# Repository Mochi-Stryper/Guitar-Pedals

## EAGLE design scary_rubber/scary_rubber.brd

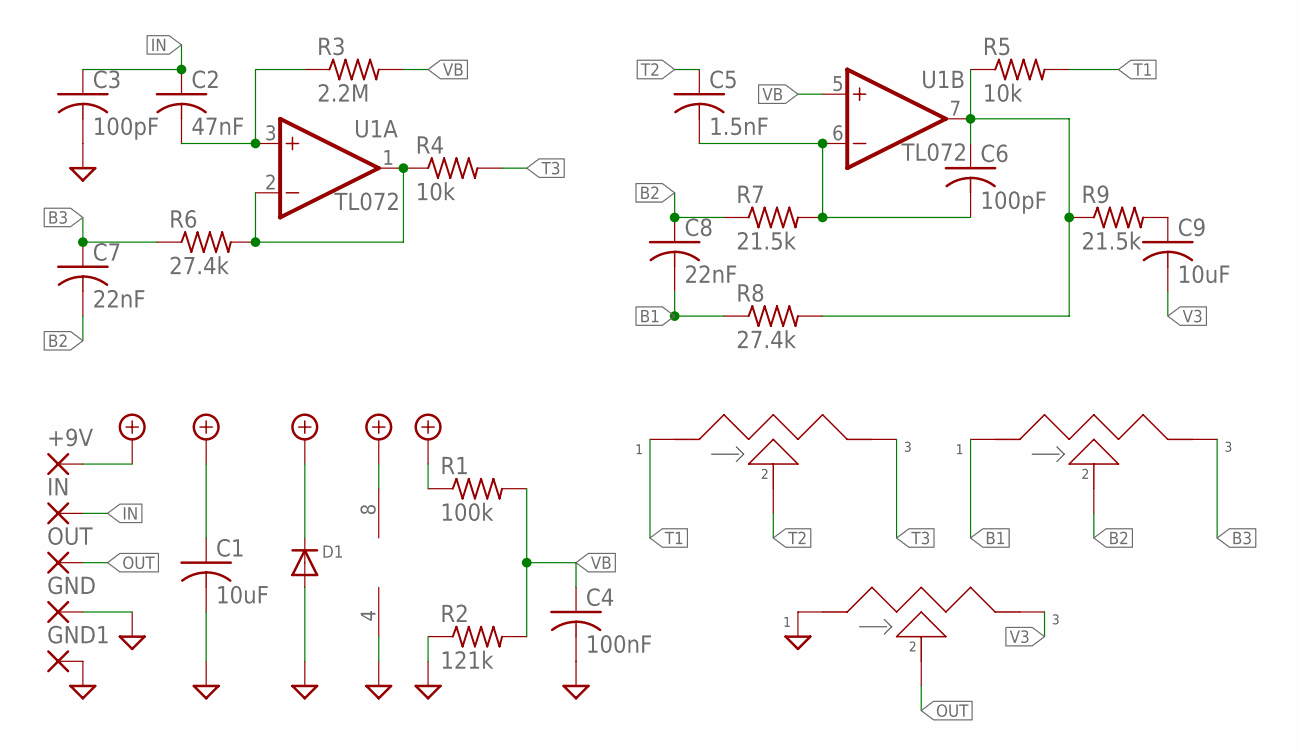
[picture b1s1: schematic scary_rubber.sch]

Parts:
+9V: SMD2; SMD1,27-2,54
BASS: B100k; POT_9MM_SMD
C1, C9: 10uF; C1206
C2: 47nF; C0603
C3, C6: 100pF; C0603
C4: 100nF; C0603
C5: 1.5nF; C0603
C7, C8: 22nF; C0603
D1: DIODESOD-123; SOD-123
GND, GND1: SMD2; SMD1,27-2,54
IN: SMD2; SMD1,27-2,54
OUT: SMD2; SMD1,27-2,54
R1: 100k; R0603
R2: 121k; R0603
R3: 2.2M; R0603
R4, R5: 10k; R0603
R6, R8: 27.4k; R0603
R7, R9: 21.5k; R0603
TREB: B100k; POT_9MM_SMD
U1: TL072; TSSOP-8
VOLU: B100k; POT_9MM_SMD

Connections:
+9V: +9V.1, C1.1, D1.C, R1.1, U1.8 (V+)
B1: BASS.1, C8.2, R8.1
B2: BASS.2, C7.2, C8.1, R7.1
B3: BASS.3, C7.1, R6.1
GND: C1.2, C3.2, C4.2, D1.A, GND.1, GND1.1, R2.1, U1.4 (V-), VOLU.1
IN: C2.1, C3.1, IN.1
unnamed: C2.2, R3.1, U1.3 (+IN)
unnamed: R4.1, R6.2, U1.1 (OUT), U1.2 (-IN)
unnamed: C5.2, C6.2, R7.2, U1.6 (-IN)
unnamed: C6.1, R5.1, R8.2, R9.1, U1.7 (OUT)
unnamed: C9.1, R9.2
OUT: OUT.1, VOLU.2
T1: R5.2, TREB.1
T2: C5.1, TREB.2
T3: R4.2, TREB.3
V3: C9.2, VOLU.3
VB: C4.1, R1.2, R2.2, R3.2, U1.5 (+IN)

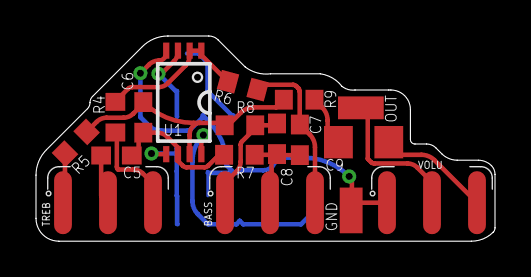
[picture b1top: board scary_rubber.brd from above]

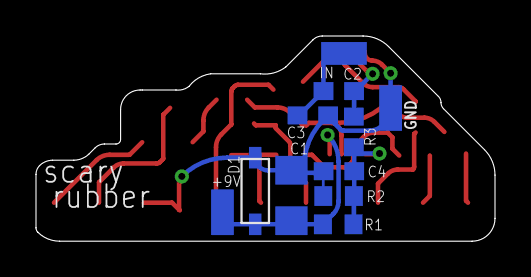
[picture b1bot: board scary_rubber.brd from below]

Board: 2 copper layers, 25.5 x 11.4 mm, 28 parts (11 on the bottom side), 17 nets.

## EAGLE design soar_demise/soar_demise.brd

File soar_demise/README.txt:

Devi Ever
Soda Meiser
Vintage Fuzz Master
The polarity of the 2907 transistor determines the sonic characteristics of the resultant fuzz. Never bent the leads on SOT23? Me neither, but give it a shot and tell me if it's worth it.
Bare bones. No tone control. No polarity protection.

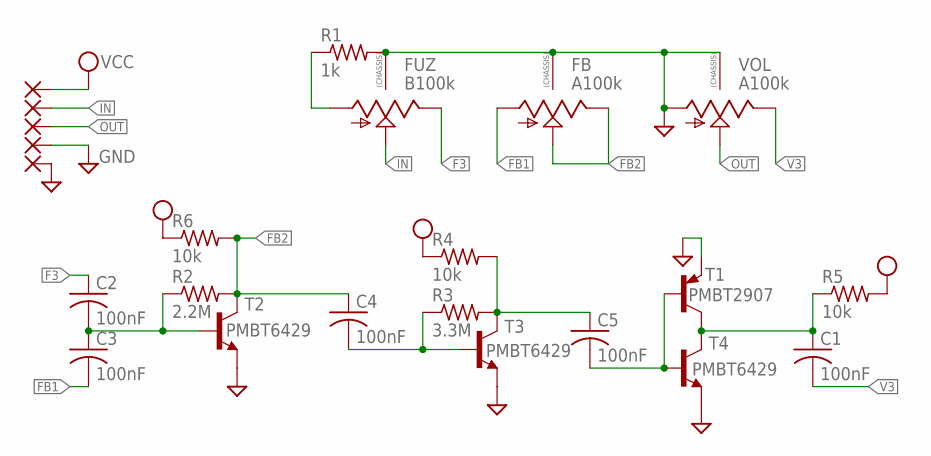
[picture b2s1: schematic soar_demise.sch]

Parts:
C1, C2, C3, C4, C5: 100nF; C0805
FB: A100k; 9MM_SNAP-IN_POT
FUZ: B100k; 9MM_SNAP-IN_POT
PAD1, PAD2, PAD3, PAD4, PAD5: 1,6/0,8
R1: 1k; R0805
R2: 2.2M; R0805
R3: 3.3M; R0805
R4, R5, R6: 10k; R0805
T1: PMBT2907; SOT23-BEC
T2, T3, T4: PMBT6429; SOT23-BEC
VOL: A100k; 9MM_SNAP-IN_POT

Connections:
F3: C2.1, FUZ.3 (E)
FB1: C3.2, FB.1 (A)
FB2: C4.1, FB.2 (S), FB.3 (E), R2.2, R6.2, T2.C
GND: FB.CHASSIS1, FB.CHASSIS2, FUZ.CHASSIS1, FUZ.CHASSIS2, PAD4.1, PAD5.1, R1.2, T1.E, T2.E, T3.E, T4.E, VOL.1 (A), VOL.CHASSIS1, VOL.CHASSIS2
IN: FUZ.2 (S), PAD2.1
unnamed: C1.1, R5.1, T1.C, T4.C
unnamed: C2.2, C3.1, R2.1, T2.B
unnamed: C5.1, R3.2, R4.2, T3.C
unnamed: FUZ.1 (A), R1.1
unnamed: C4.2, R3.1, T3.B
unnamed: C5.2, T1.B, T4.B
OUT: PAD3.1, VOL.2 (S)
V3: C1.2, VOL.3 (E)
VCC: PAD1.1, R4.1, R5.2, R6.1

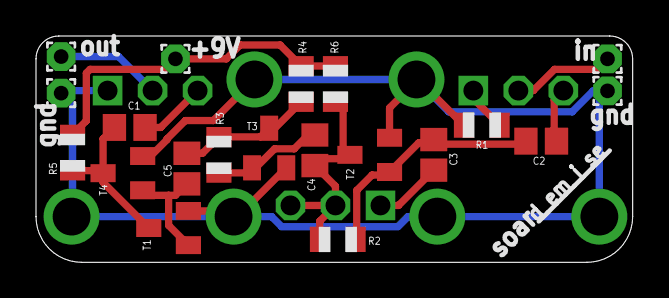
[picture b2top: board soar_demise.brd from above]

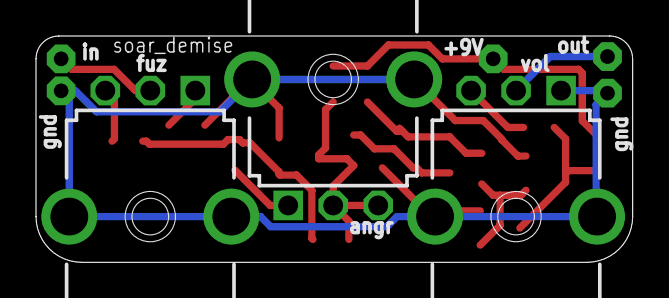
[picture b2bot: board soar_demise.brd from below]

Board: 2 copper layers, 33.1 x 12.6 mm, 23 parts (3 on the bottom side), 14 nets.

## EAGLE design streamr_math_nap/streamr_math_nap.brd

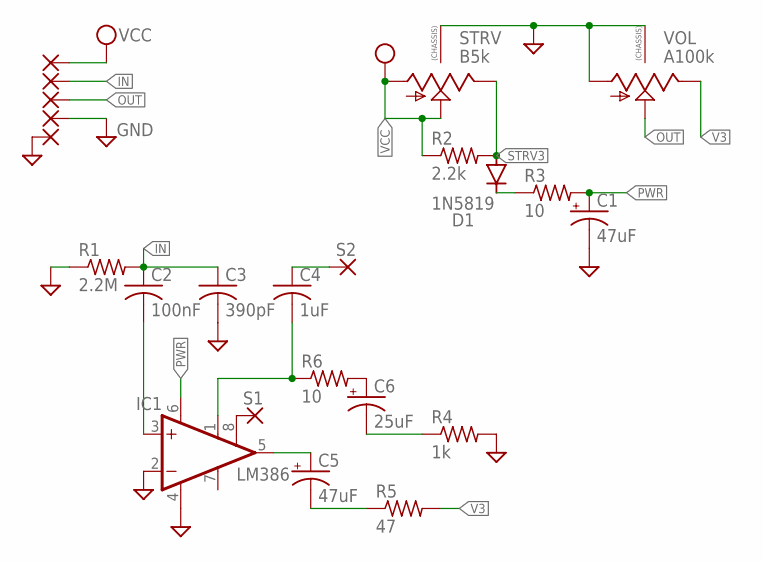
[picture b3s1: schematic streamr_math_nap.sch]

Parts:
C1, C5: 47uF; PAN_C_SMD+THRU
C2: 100nF; C0805
C3: 390pF; C0805
C4: 1uF; C0805
C6: 25uF; PAN_C_SMD+THRU
D1: 1N5819; SOD123
IC1: LM386; SO08
PAD1, PAD2, PAD3, PAD4, PAD5: 1,6/0,8
R1: 2.2M; R0805
R2: 2.2k; R1206
R3, R6: 10; R1206
R4: 1k; R1206
R5: 47; R1206
S1: S1; 1,6/0,8
S2: S2; 1,6/0,8
STRV: B5k; 9MM_SNAP-IN_POT
VOL: A100k; 9MM_SNAP-IN_POT

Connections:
GND: C1.-, C1.-- (-), C3.2, IC1.2 (-IN), IC1.4 (GND), PAD4.1, PAD5.1, R1.1, R4.2, STRV.CHASSIS1, STRV.CHASSIS2, VOL.1 (A), VOL.CHASSIS1, VOL.CHASSIS2
IN: C2.1, C3.1, PAD2.1, R1.2
unnamed: IC1.8 (GAIN), S1.1
unnamed: C2.2, IC1.3 (+IN)
unnamed: D1.C, R3.1
unnamed: C4.2, IC1.1 (GAIN), R6.1
unnamed: C5.+, C5.++ (+), IC1.5 (OUT)
unnamed: C5.-, C5.-- (-), R5.1
unnamed: C6.+, C6.++ (+), R6.2
unnamed: C6.-, C6.-- (-), R4.1
unnamed: C4.1, S2.1
OUT: PAD3.1, VOL.2 (S)
PWR: C1.+, C1.++ (+), IC1.6 (VS), R3.2
STRV3: D1.A, R2.2, STRV.3 (E)
V3: R5.2, VOL.3 (E)
VCC: PAD1.1, R2.1, STRV.1 (A), STRV.2 (S)

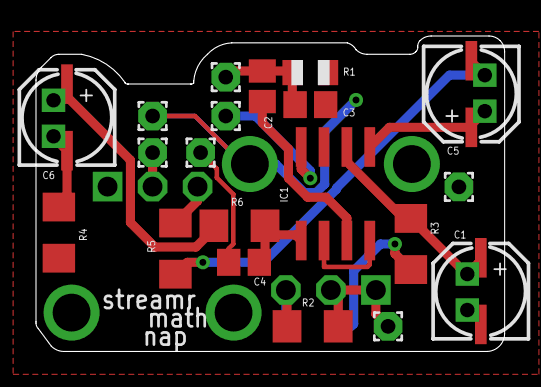
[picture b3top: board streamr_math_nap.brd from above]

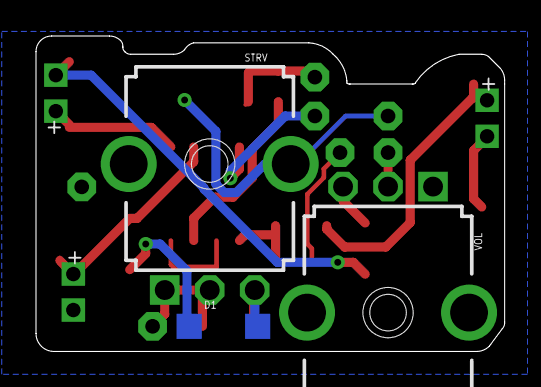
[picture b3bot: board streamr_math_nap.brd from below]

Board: 2 copper layers, 26.0 x 17.5 mm, 23 parts (3 on the bottom side), 16 nets.

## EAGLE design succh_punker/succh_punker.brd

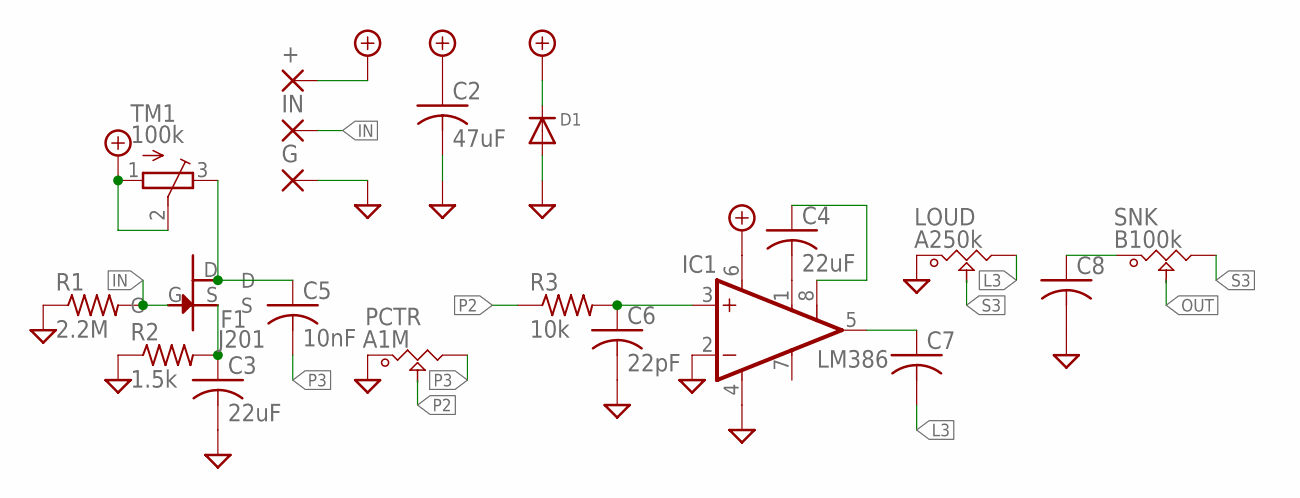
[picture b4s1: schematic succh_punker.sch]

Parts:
+: SMD2; SMD1,27-2,54
C2: 47uF; C1210
C3, C4: 22uF; C1210
C5: 10nF; C0603
C6: 22pF; C0603
C7, C8: C-USC0603; C0603
D1: DIODESOD-123; SOD-123
F1: J201; MMBFJ201
G: SMD2; SMD1,27-2,54
IC1: LM386; SO08
IN: SMD2; SMD1,27-2,54
LOUD: A250k; POT_9MM_SMD
PCTR: A1M; POT_9MM_SMD
R1: 2.2M; R0603
R2: 1.5k; R0603
R3: 10k; R0603
SNK: B100k; POT_9MM_SMD
TM1: 100k; TC33X

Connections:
+9V: +.1, C2.1, D1.C, IC1.6 (VS), TM1.1 (A), TM1.2 (S)
F1_D: C5.1, F1.D, TM1.3 (E)
F1_S: C3.1, F1.S, R2.2
GND: C2.2, C3.2, C6.2, C8.2, D1.A, G.1, IC1.2 (-IN), IC1.4 (GND), LOUD.1, PCTR.1, R1.1, R2.1
IN: F1.G, IN.1, R1.2
L3: C7.2, LOUD.3
unnamed: C4.2, IC1.1 (GAIN)
unnamed: C8.1, SNK.1
unnamed: C4.1, IC1.8 (GAIN)
OA_+: C6.1, IC1.3 (+IN), R3.2
OA_O: C7.1, IC1.5 (OUT)
OUT: SNK.2
P2: PCTR.2, R3.1
P3: C5.2, PCTR.3
S3: LOUD.2, SNK.3

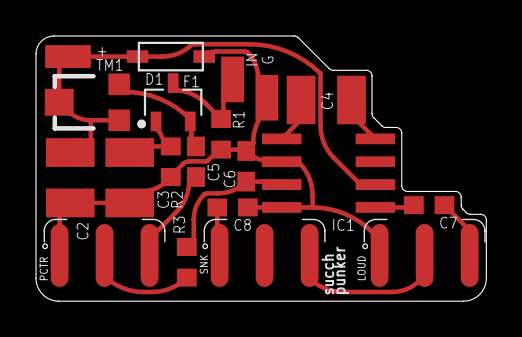
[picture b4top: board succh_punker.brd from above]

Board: 2 copper layers, 25.0 x 14.7 mm, 20 parts (0 on the bottom side), 14 nets.

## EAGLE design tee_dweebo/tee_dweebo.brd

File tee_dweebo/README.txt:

Boss
BD-2 Blues Driver
Notes:
Registered an airwire across the lugs of the DRV pot. This should be resolved via the pot's chassis ground. However, if an external potentiometer is used, then it's advisable to run a ground airwire to the chassis lugs. Best of luck.

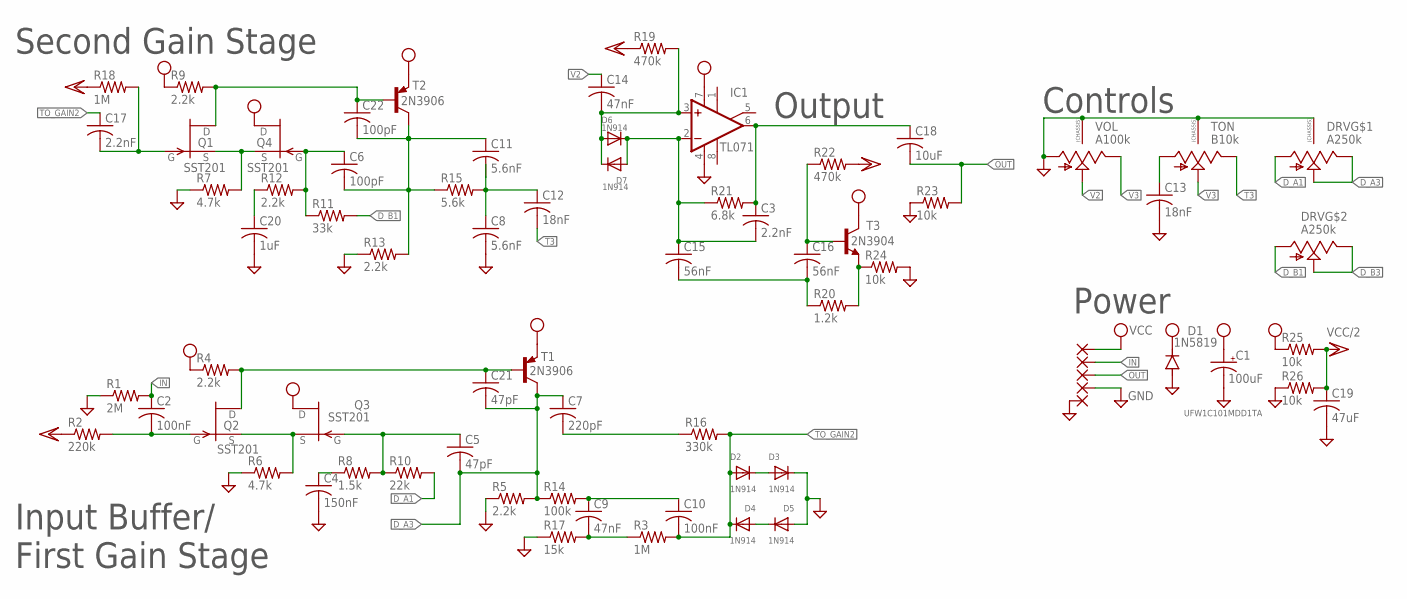
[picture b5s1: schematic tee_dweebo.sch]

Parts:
C1: 100uF; ELEC10UF_SM
C2, C10: 100nF; C0402
C3, C17: 2.2nF; C0402
C4: 150nF; C0402
C5, C21: 47pF; C0402
C6, C22: 100pF; C0402
C7: 220pF; C0402
C8, C11: 5.6nF; C0402
C9, C14: 47nF; C0402
C12, C13: 18nF; C0402
C15, C16: 56nF; C0402
C18: 10uF; C0805
C19: 47uF; C1206
C20: 1uF; C0603
D1: 1N5819; SOD123
D2, D3, D4, D5, D6, D7: 1N914; SOD-323F
DRV: A250k; DUAL_9MM_SNAP-IN_POT
IC1: TL071; SO08
PAD1, PAD2, PAD3, PAD4, PAD5: 1,6/0,8
Q1, Q2, Q3, Q4: SST201; SOT23
R1: 2M; R0402
R2: 220k; R0402
R3, R18: 1M; R0402
R4, R5, R9, R12, R13: 2.2k; R0402
R6, R7: 4.7k; R0402
R8: 1.5k; R0402
R10: 22k; R0402
R11: 33k; R0402
R14: 100k; R0402
R15: 5.6k; R0402
R16: 330k; R0402
R17: 15k; R0402
R19, R22: 470k; R0402
R20: 1.2k; R0402
R21: 6.8k; R0402
R23, R24, R25, R26: 10k; R0402
T1, T2: 2N3906; SOT23-BEC
T3: 2N3904; SOT23-BEC
TON: B10k; 9MM_SNAP-IN_POT
VOL: A100k; 9MM_SNAP-IN_POT

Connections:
D_A1: DRV.1 (A), R10.2
D_A3: C5.2, C7.1, C21.2, DRV.2 (S), DRV.3 (E), R5.2, R14.1, T1.C
D_B1: DRV.1B (A), R11.2
D_B3: DRV.2B (S), DRV.3B (E)
GND: C1.-, C4.2, C8.2, C13.2, C19.2, C20.2, D1.A, D3.C, D5.A, DRV.CHASSIS1, DRV.CHASSIS2, IC1.4 (V-), PAD4.1, PAD5.1, R1.1, R5.1, R6.1, R7.1, R13.1, R17.1, R23.1, R24.2, R26.1, TON.CHASSIS1, TON.CHASSIS2, VOL.1 (A), VOL.CHASSIS1, VOL.CHASSIS2
IN: C2.1, PAD2.1, R1.2
unnamed: Q2.2 (S), Q3.2 (S), R6.2
unnamed: C2.2, Q2.3 (G), R2.2
unnamed: C21.1, Q2.1 (D), R4.2, T1.B
unnamed: C4.1, R8.1
unnamed: C5.1, Q3.3 (G), R8.2, R10.1
unnamed: C9.1, C10.1, R14.2
unnamed: C9.2, R3.1, R17.2
unnamed: C17.2, Q1.3 (G), R18.2
unnamed: C7.2, R16.1
unnamed: D2.C, D3.A
unnamed: D4.A, D5.C
unnamed: C22.1, Q1.1 (D), R9.2, T2.B
unnamed: Q1.2 (S), Q4.2 (S), R7.2
unnamed: C6.1, Q4.3 (G), R11.1, R12.2
unnamed: C20.1, R12.1
unnamed: C8.1, C11.2, C12.1, R15.2
unnamed: C6.2, C11.1, C22.2, R13.2, R15.1, T2.C
unnamed: C13.1, TON.1 (A)
unnamed: C14.2, D6.A, D7.C, IC1.3 (+IN), R19.2
unnamed: C3.2, C15.1, D6.C, D7.A, IC1.2 (-IN), R21.1
unnamed: C3.1, C18.1, IC1.6 (OUT), R21.2
unnamed: C16.1, R22.1, T3.B
unnamed: C15.2, C16.2, R20.1
unnamed: R20.2, R24.1, T3.E
OUT: C18.2, PAD3.1, R23.2
T3: C12.2, TON.3 (E)
TO_GAIN2: C10.2, C17.1, D2.A, D4.C, R3.2, R16.2
V2: C14.1, VOL.2 (S)
V3: TON.2 (S), VOL.3 (E)
VCC: C1.+, D1.C, IC1.7 (V+), PAD1.1, Q3.1 (D), Q4.1 (D), R4.1, R9.1, R25.1, T1.E, T2.E, T3.C
VCC/2: C19.1, R2.1, R18.1, R19.1, R22.2, R25.2, R26.2

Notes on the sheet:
Input Buffer/ First Gain Stage
Second Gain Stage
Output
Controls
Power

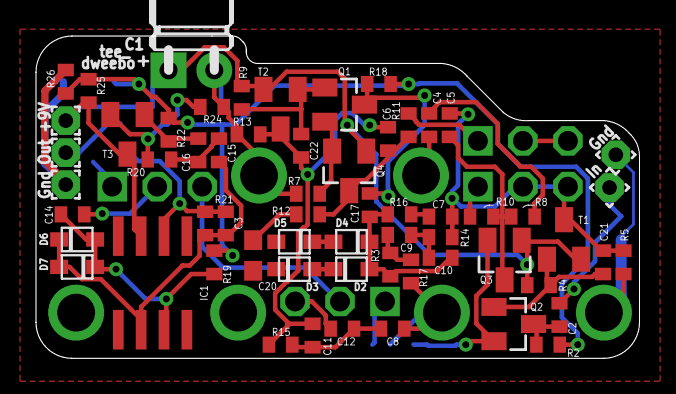
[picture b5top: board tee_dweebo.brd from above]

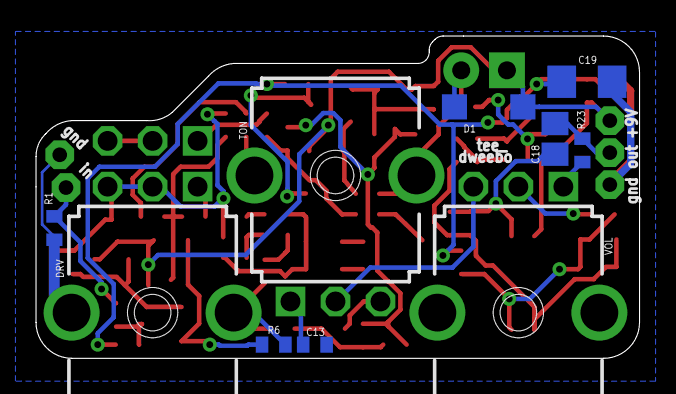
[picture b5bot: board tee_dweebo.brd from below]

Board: 2 copper layers, 33.5 x 17.9 mm, 71 parts (10 on the bottom side), 37 nets.

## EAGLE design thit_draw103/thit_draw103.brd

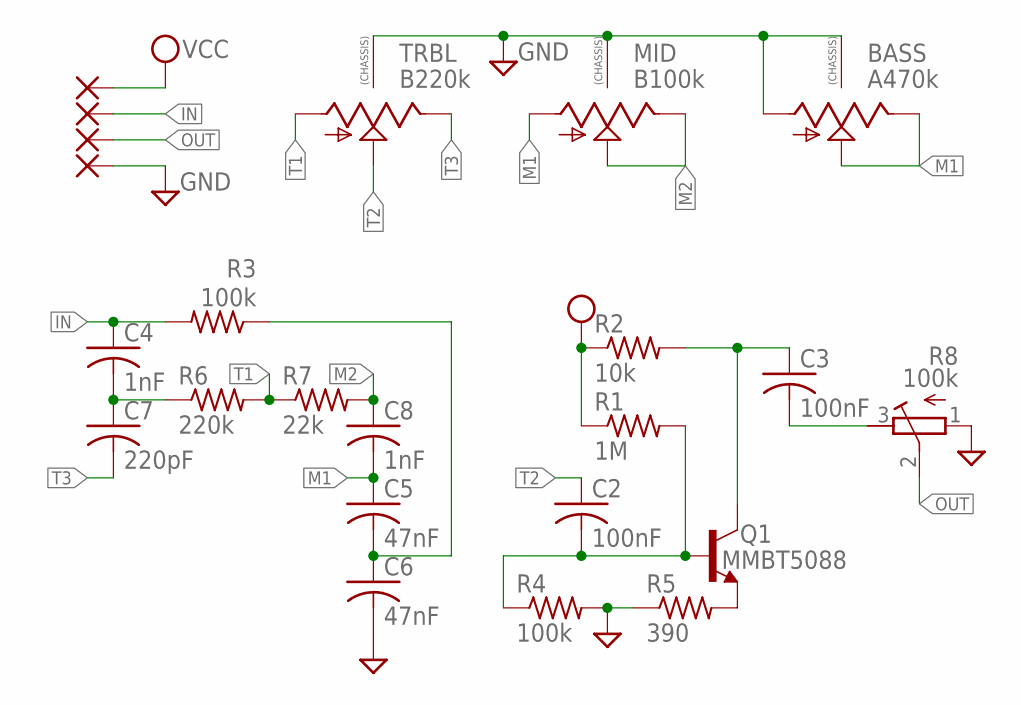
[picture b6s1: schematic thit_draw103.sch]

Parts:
BASS: A470k; 9MM_SNAP-IN_POT
C2, C3: 100nF; C0603
C4, C8: 1nF; C0603
C5, C6: 47nF; C0603
C7: 220pF; C0603
MID: B100k; 9MM_SNAP-IN_POT
PAD1, PAD2, PAD3, PAD4: 1,6/0,8
Q1: MMBT5088; SOT23-BEC
R1: 1M; R0603
R2: 10k; R0603
R3, R4: 100k; R0603
R5: 390; R0603
R6: 220k; R0603
R7: 22k; R0603
R8: 100k; RTRIM3224X
TRBL: B220k; 9MM_SNAP-IN_POT

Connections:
GND: BASS.1 (A), BASS.CHASSIS1, BASS.CHASSIS2, C6.2, MID.CHASSIS1, MID.CHASSIS2, PAD4.1, R4.2, R5.1, R8.1 (A), TRBL.CHASSIS1, TRBL.CHASSIS2
IN: C4.1, PAD2.1, R3.2
M1: BASS.2 (S), BASS.3 (E), C5.1, C8.2, MID.1 (A)
M2: C8.1, MID.2 (S), MID.3 (E), R7.2
unnamed: C2.2, Q1.B, R1.2, R4.1
unnamed: C4.2, C7.1, R6.1
unnamed: C5.2, C6.1, R3.1
unnamed: Q1.E, R5.2
unnamed: C3.1, Q1.C, R2.2
unnamed: C3.2, R8.3 (E)
OUT: PAD3.1, R8.2 (S)
T1: R6.2, R7.1, TRBL.1 (A)
T2: C2.1, TRBL.2 (S)
T3: C7.2, TRBL.3 (E)
VCC: PAD1.1, R1.1, R2.1

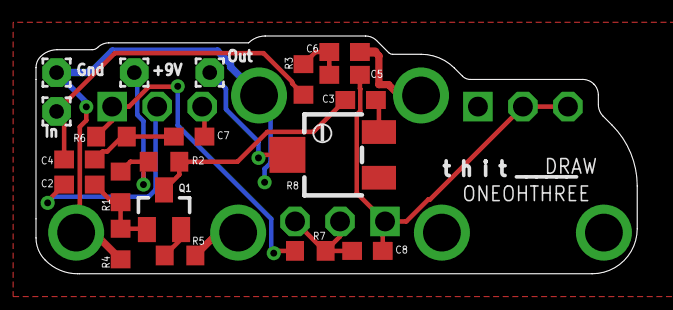
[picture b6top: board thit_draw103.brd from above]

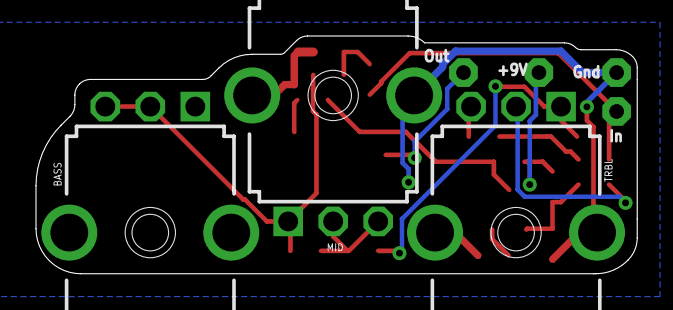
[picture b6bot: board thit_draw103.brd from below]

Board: 2 copper layers, 33.4 x 13.2 mm, 23 parts (3 on the bottom side), 15 nets.

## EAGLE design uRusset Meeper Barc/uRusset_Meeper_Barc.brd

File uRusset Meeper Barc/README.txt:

Ibanez
Super Tube Screamer
Offboard:
C20k Dual-Gang "Mids" Potentiometer
Notes:
Clipping Diodes swapped with BAT54S

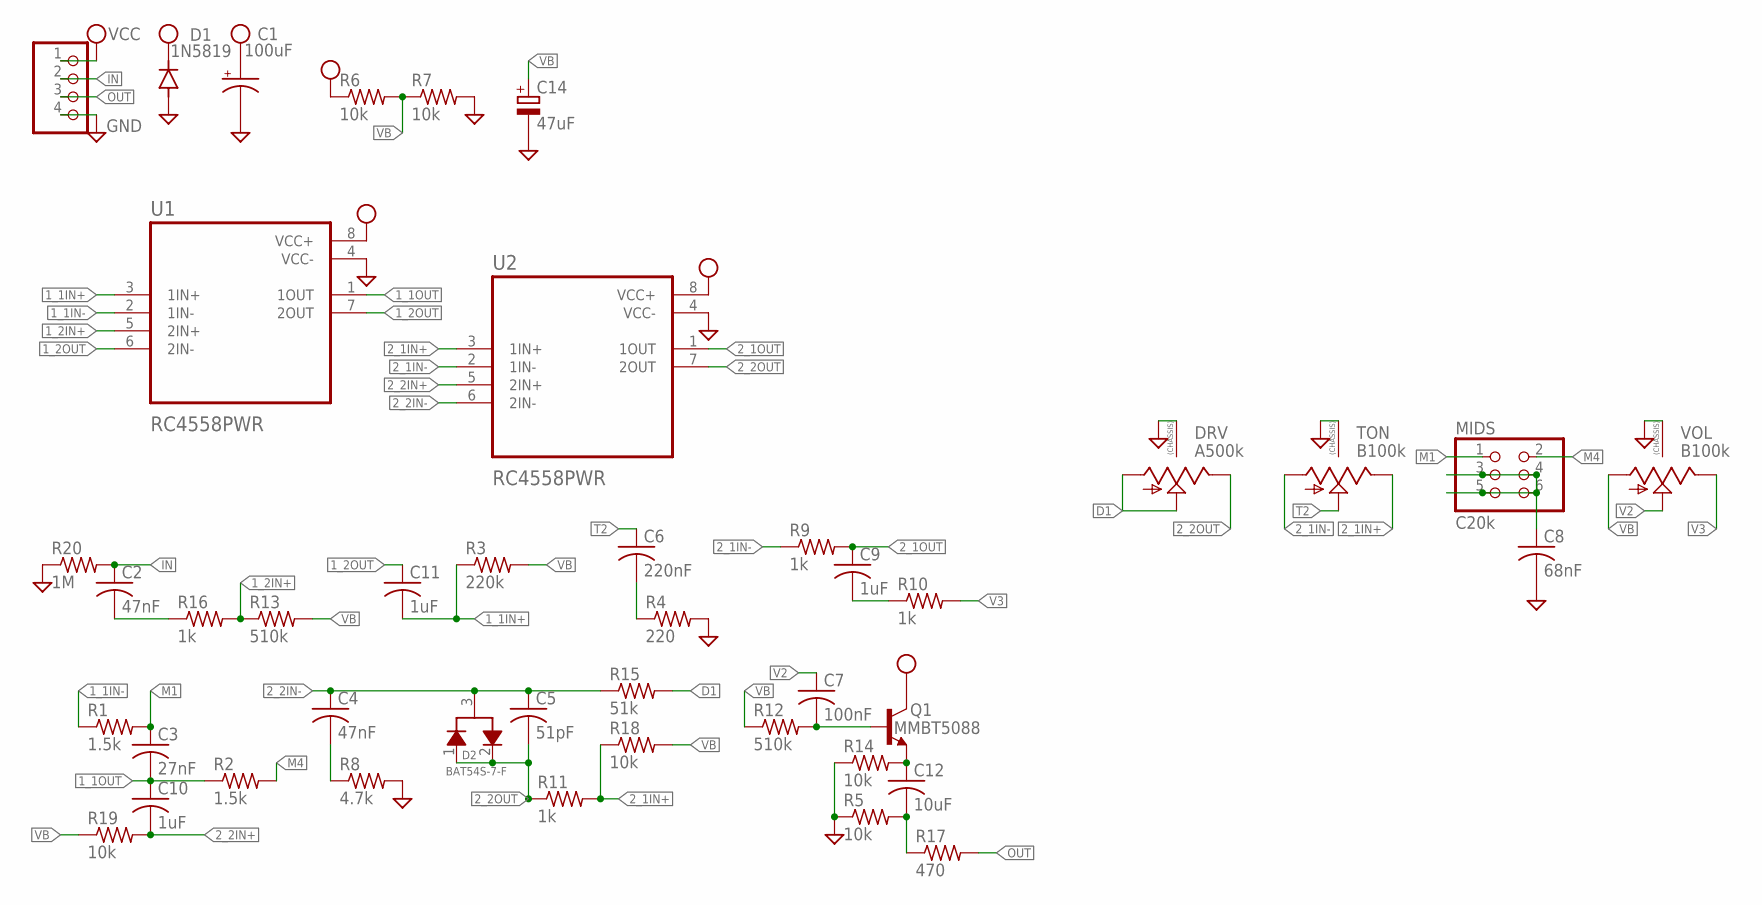
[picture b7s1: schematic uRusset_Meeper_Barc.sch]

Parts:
C1: 100uF; PAN_B_SMD+THRU
C2, C4: 47nF; C0603
C3: 27nF; C0603
C5: 51pF; C0603
C6: 220nF; C0603
C7: 100nF; C0603
C8: 68nF; C0603
C9, C10, C11: 1uF; C0805
C12: 10uF; C1206
C14: 47uF; CAPMP3216X180N
D1: 1N5819; SOD123
D2: BAT54S-7-F; SOT23-3
DRV: A500k; 9MM_SNAP-IN_POT
JP1: PINHD-1X4; 1X04
MIDS: C20k; 2X03
Q1: MMBT5088; SOT23-BEC
R1, R2: 1.5k; R0603
R3: 220k; R0603
R4: 220; R0603
R5, R6, R7, R14, R18, R19: 10k; R0603
R8: 4.7k; R0603
R9, R10, R11, R16: 1k; R0603
R12, R13: 510k; R0603
R15: 51k; R0603
R17: 470; R0603
R20: 1M; R0603
TON: B100k; 9MM_SNAP-IN_POT
U1, U2: RC4558PWR; SOP65P640X120-8N
VOL: B100k; 9MM_SNAP-IN_POT

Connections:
1_1IN+: C11.2, R3.1, U1.3 (1IN+)
1_1IN-: R1.1, U1.2 (1IN-)
1_1OUT: C3.2, C10.1, R2.1, U1.1 (1OUT)
1_2IN+: R13.1, R16.2, U1.5 (2IN+)
1_2OUT: C11.1, U1.6 (2IN-), U1.7 (2OUT)
2_1IN+: R11.2, R18.1, TON.3 (E), U2.3 (1IN+)
2_1IN-: R9.1, TON.1 (A), U2.2 (1IN-)
2_1OUT: C9.1, R9.2, U2.1 (1OUT)
2_2IN+: C10.2, R19.2, U2.5 (2IN+)
2_2IN-: C4.1, C5.1, D2.3, R15.1, U2.6 (2IN-)
2_2OUT: C5.2, D2.1, D2.2, DRV.3 (E), R11.1, U2.7 (2OUT)
D1: DRV.1 (A), DRV.2 (S), R15.2
GND: C1.-, C1.-- (-), C8.2, C14.2 (-), D1.A, DRV.CHASSIS1, DRV.CHASSIS2, JP1.4, R4.2, R5.1, R7.2, R8.2, R14.1, R20.1, TON.CHASSIS1, TON.CHASSIS2, U1.4 (VCC-), U2.4 (VCC-), VOL.CHASSIS1, VOL.CHASSIS2
IN: C2.1, JP1.2, R20.2
M1: C3.1, MIDS.1, R1.2
M4: MIDS.2, R2.2
unnamed: C8.1, MIDS.3, MIDS.4, MIDS.5, MIDS.6
unnamed: C4.2, R8.1
unnamed: C2.2, R16.1
unnamed: C6.2, R4.1
unnamed: C9.2, R10.1
unnamed: C7.2, Q1.B, R12.2
unnamed: C12.1, Q1.E, R14.2
unnamed: C12.2, R5.2, R17.1
OUT: JP1.3, R17.2
T2: C6.1, TON.2 (S)
V2: C7.1, VOL.2 (S)
V3: R10.2, VOL.3 (E)
VB: C14.1 (+), R3.2, R6.2, R7.1, R12.1, R13.2, R18.2, R19.1, VOL.1 (A)
VCC: C1.+, C1.++ (+), D1.C, JP1.1, Q1.C, R6.1, U1.8 (VCC+), U2.8 (VCC+)

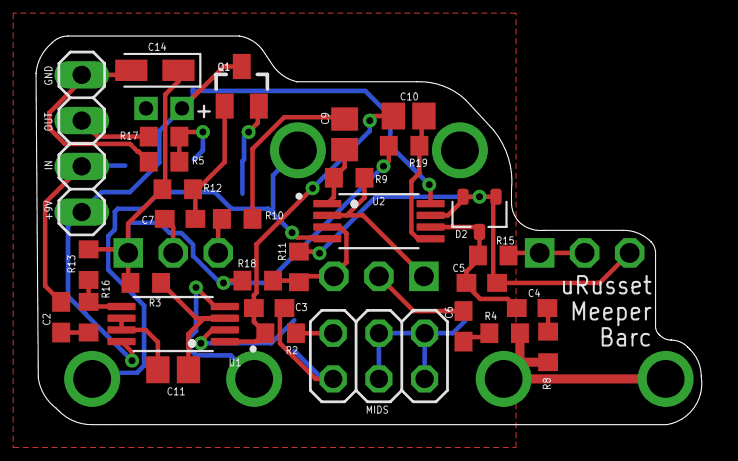
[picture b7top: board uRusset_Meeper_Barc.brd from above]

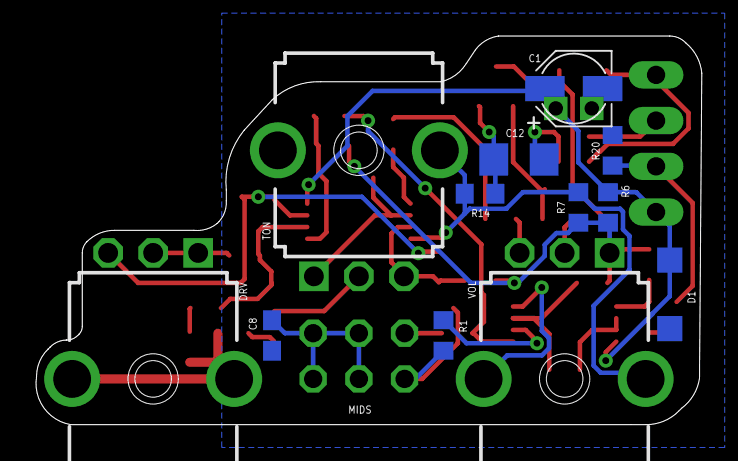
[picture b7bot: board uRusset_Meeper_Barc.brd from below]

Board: 2 copper layers, 37.0 x 21.6 mm, 43 parts (12 on the bottom side), 30 nets.

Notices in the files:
parts and their libraries:
SparkFun-Aesthetics: Licensing: Creative Commons ShareAlike 4.0 International - https://creativecommons.org/licenses/by-sa/4.0
